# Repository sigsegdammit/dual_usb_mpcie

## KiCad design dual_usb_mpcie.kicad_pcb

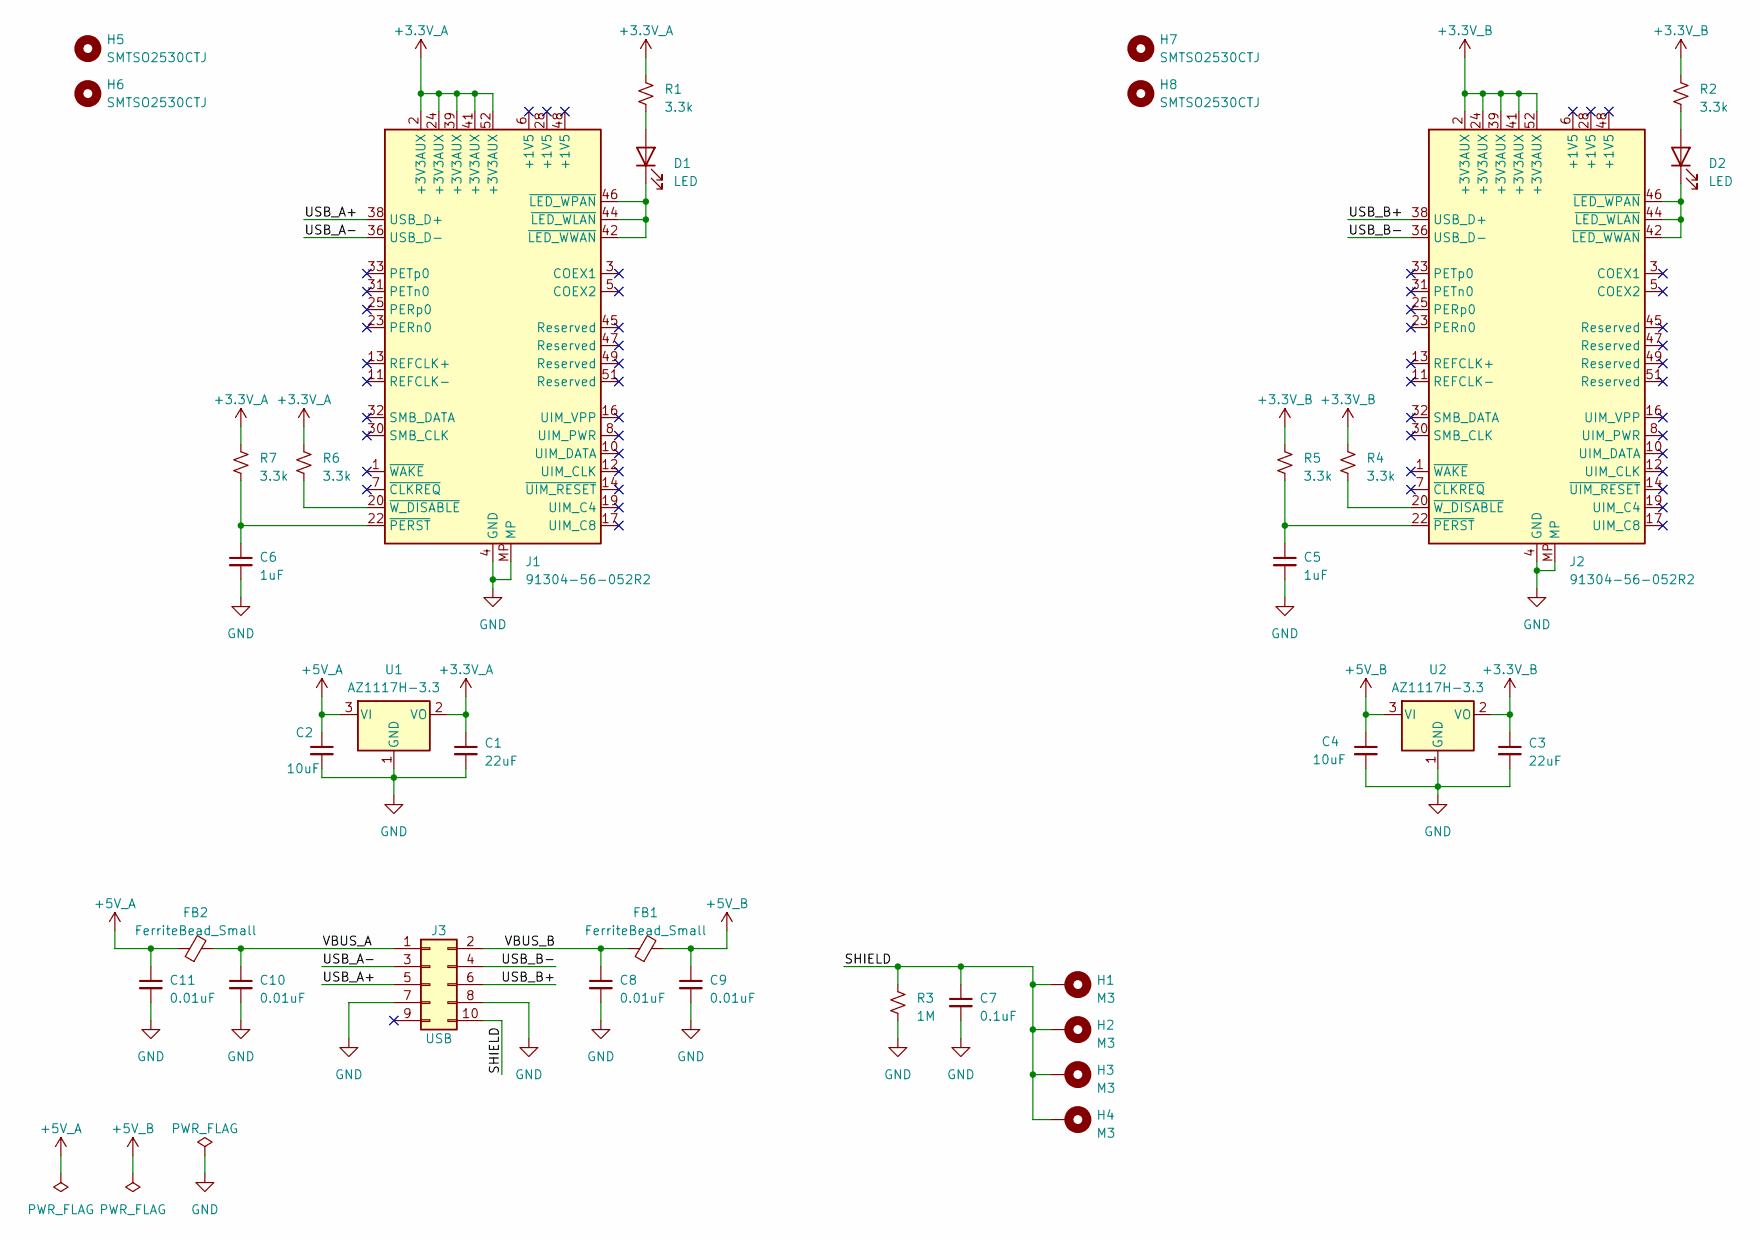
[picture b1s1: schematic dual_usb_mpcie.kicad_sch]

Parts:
C1, C3: 22uF; C_1206_3216Metric; LCSC C12891
C2, C4: 10uF; C_1206_3216Metric; LCSC C13585
C5, C6: 1uF; C_0603_1608Metric; LCSC C15849
C7: 0.1uF; C_0603_1608Metric; LCSC C14663
C8, C9, C10, C11: 0.01uF; C_0603_1608Metric; LCSC C57112
D1, D2: LED; LED_0603_1608Metric; LCSC C72041
FB1, FB2: FerriteBead_Small; L_0805_2012Metric; LCSC C1017
H1, H2, H3, H4: M3; MountingHole_3.2mm_M3_Pad
H5, H6, H7, H8: SMTSO2530CTJ; SMTSO25; LCSC C2915631
J1, J2: 91304-56-052R2; BUS_PCI_Express_Mini_Full; LCSC C404121
J3: USB; PinHeader_2x05_P2.54mm_Vertical_SMD; LCSC C3294463
R1, R2, R4, R5, R6, R7: 3.3k; R_0603_1608Metric; LCSC C22978
R3: 1M; R_0603_1608Metric; LCSC C22935
U1, U2: AZ1117H-3.3; SOT-223-3_TabPin2; LCSC C92517

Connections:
+3.3V_A: C1.1, J1.2 (+3V3AUX), J1.24 (+3V3AUX), J1.39 (+3V3AUX), J1.41 (+3V3AUX), J1.52 (+3V3AUX), R1.1, R6.1, R7.1, U1.2 (VO)
+3.3V_B: C3.1, J2.2 (+3V3AUX), J2.24 (+3V3AUX), J2.39 (+3V3AUX), J2.41 (+3V3AUX), J2.52 (+3V3AUX), R2.1, R4.1, R5.1, U2.2 (VO)
+5V_A: C2.1, C11.1, FB2.1, U1.3 (VI)
+5V_B: C4.1, C9.1, FB1.2, U2.3 (VI)
/SHIELD: C7.1, H1.1, H2.1, H3.1, H4.1, J3.10, R3.1
/USB_A+: J1.38 (USB_D+), J3.5
/USB_A-: J1.36 (USB_D-), J3.3
/USB_B+: J2.38 (USB_D+), J3.6
/USB_B-: J2.36 (USB_D-), J3.4
/VBUS_A: C10.1, FB2.2, J3.1
/VBUS_B: C8.1, FB1.1, J3.2
GND: C1.2, C2.2, C3.2, C4.2, C5.2, C6.2, C7.2, C8.2, C9.2, C10.2, C11.2, J1.4 (GND), J1.9 (GND), J1.15 (GND), J1.18 (GND), J1.21 (GND), J1.26 (GND), J1.27 (GND), J1.29 (GND), J1.34 (GND), J1.35 (GND), J1.37 (GND), J1.40 (GND), J1.43 (GND), J1.50 (GND), J1.MP, J2.4 (GND), J2.9 (GND), J2.15 (GND), J2.18 (GND), J2.21 (GND), J2.26 (GND), J2.27 (GND), J2.29 (GND), J2.34 (GND), J2.35 (GND), J2.37 (GND), J2.40 (GND), J2.43 (GND), J2.50 (GND), J2.MP, J3.7, J3.8, R3.2, U1.1 (GND), U2.1 (GND)
unnamed: D1.2 (A), R1.2
unnamed: D1.1 (K), J1.42 (~LED_WWAN), J1.44 (~LED_WLAN), J1.46 (~LED_WPAN)
unnamed: D2.2 (A), R2.2
unnamed: D2.1 (K), J2.42 (~LED_WWAN), J2.44 (~LED_WLAN), J2.46 (~LED_WPAN)
unnamed: C6.1, J1.22 (~PERST), R7.2
unnamed: J1.20 (~W_DISABLE), R6.2
unnamed: C5.1, J2.22 (~PERST), R5.2
unnamed: J2.20 (~W_DISABLE), R4.2

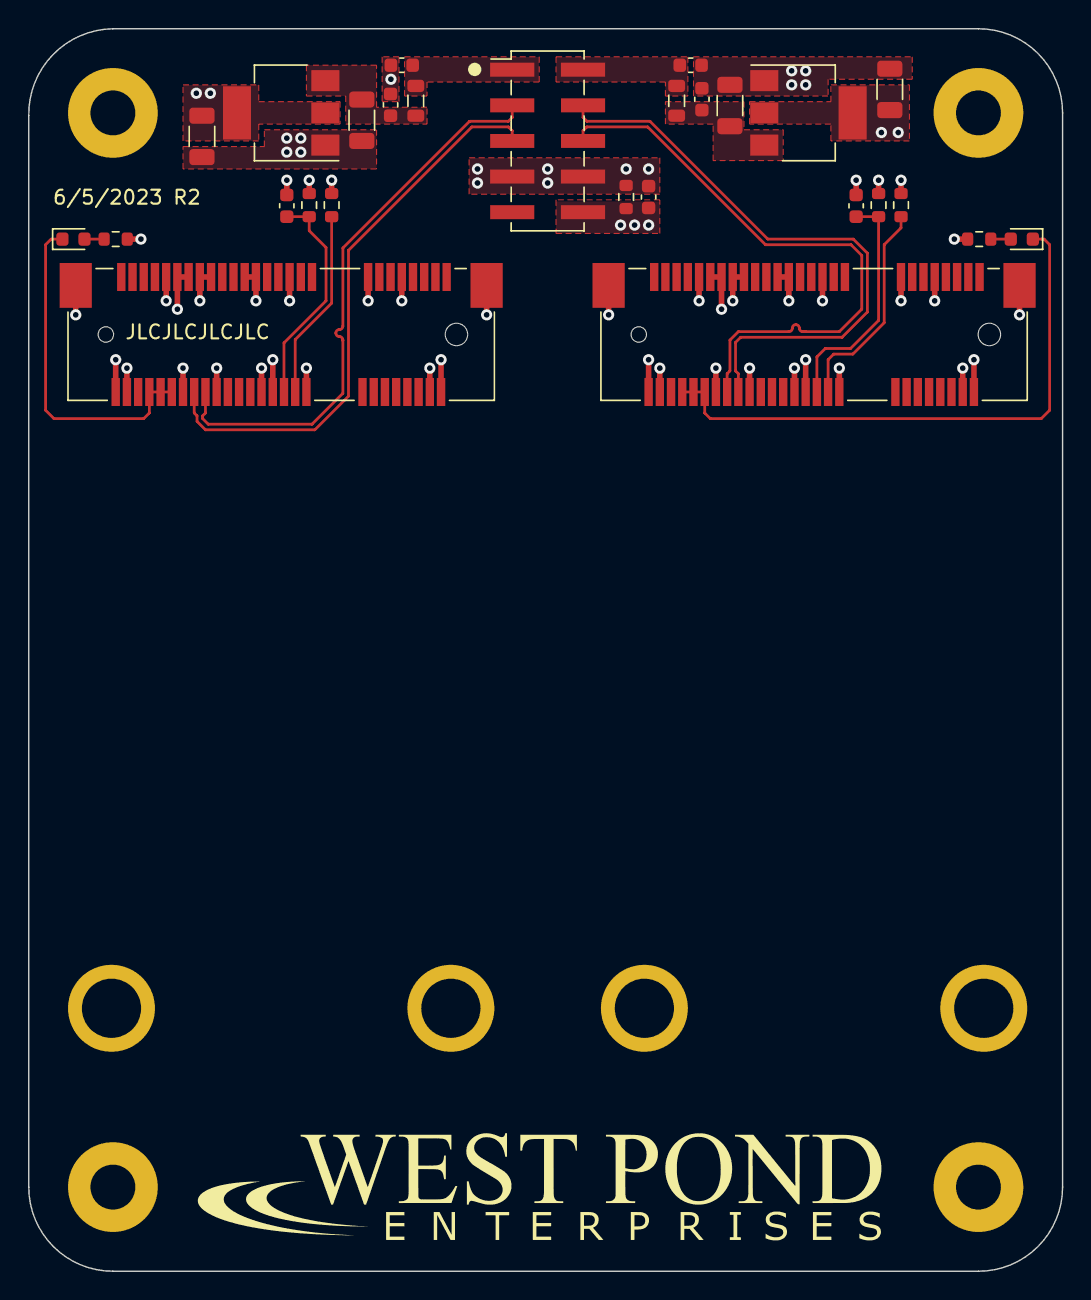
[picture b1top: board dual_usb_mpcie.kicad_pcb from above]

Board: 4 copper layers, 73.7 x 88.6 mm, 35 parts (0 on the bottom side), 20 nets.

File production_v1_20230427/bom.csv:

Designator,Footprint,Quantity,Value,LCSC Part #
"C1, C3, C5, C6",1206,4,22uF,C12891
"C2, C4",1206,2,10uF,C13585
"D1, D2",0603,2,LED,C72041
"FID1, FID2, FID3",fiducial_jlcpcb_smt,3,Fiducial,
"H1, H2, H3, H4",MountingHole_3.2mm_M3_Pad,4,M3,
"H5, H6, H7, H8",SMTSO25,4,SMTSO2530CTJ,C2915631
"J1, J2",BUS_PCI_Express_Mini_Full,2,91304-56-052R2,C404121
J3,PinHeader_2x05_P2.54mm_Vertical_SMD,1,USB,C3294463
"R1, R2",0603,2,3.3k,C22978
"U1, U2",SOT-223-3_TabPin2,2,AZ1117H-3.3,C92517
"U3, U4",SOT-223-3_TabPin2,2,AZ1117H-1.5,C526403

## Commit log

2023-04-27 Initial commit. Completed design and layout.
2023-04-27 V1 production files
2023-05-21 Remove 1.5v. Change bottom pour to shield. Couple shield with ground. Add pull-up to W_DIS and PCIE_RST.
2023-05-30 Rotate mpcie connectors so all routing is at the top of the board. Move power to the top. Move up mpcie connectors. Add silkscreen. Add models to mpcie and standoff
2023-06-06 WPE logo
2023-06-06 Fix FB size for part. 0603 -> 0805
2023-06-06 As sent to fab
